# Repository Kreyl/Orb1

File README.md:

# Orb1

Project for shining orb with ws2818 leds and radio

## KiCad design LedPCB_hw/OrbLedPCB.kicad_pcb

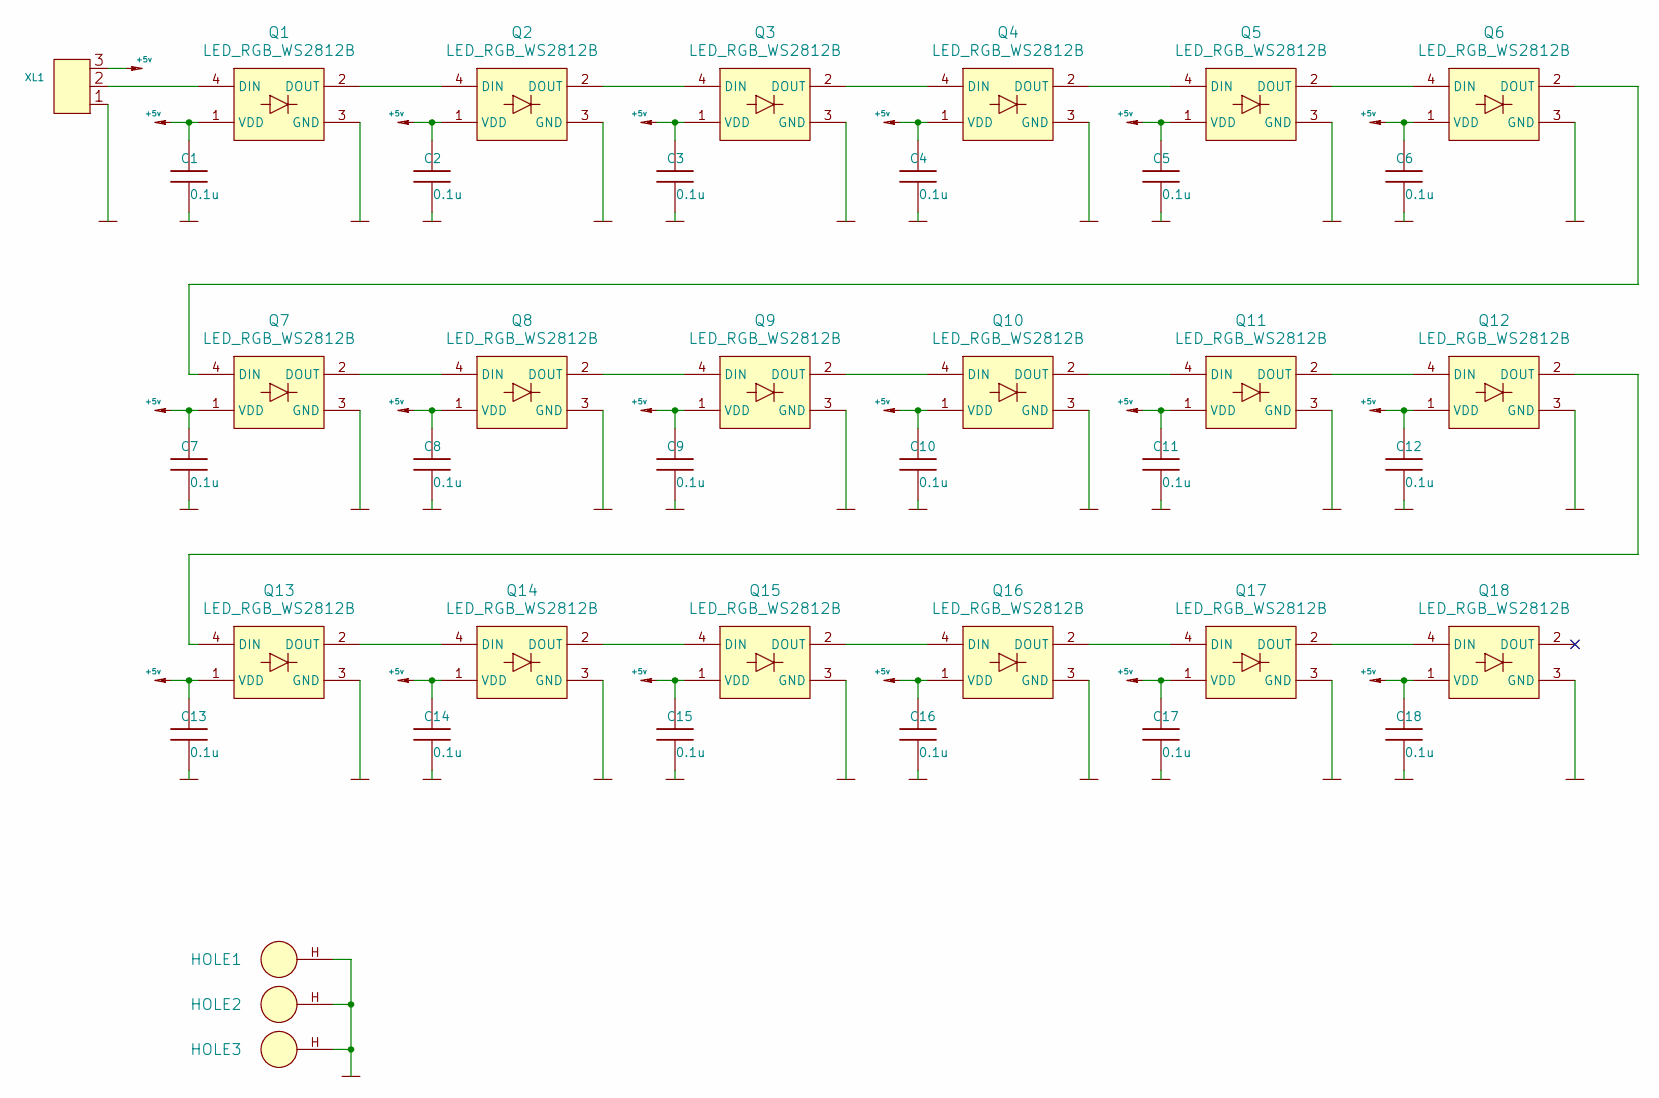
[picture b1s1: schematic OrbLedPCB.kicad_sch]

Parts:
C1, C2, C3, C4, C5, C6, C7, C8, C9, C10, C11, C12, C13, C14, C15, C16, C17, C18: 0.1u; CAP_0603_Silks; Tolerance 20%
HOLE1, HOLE2, HOLE3: HOLE_METALLED; Hole2d2_out3d5mm
Q1, Q2, Q3, Q4, Q5, Q6, Q7, Q8, Q9, Q10, Q11, Q12, Q13, Q14, Q15, Q16, Q17, Q18: LED_RGB_WS2812B; LED_WS2812B
XL1: CONN_3; WB-03(MW-3M)

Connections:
+5v: C1.1, C2.1, C3.1, C4.1, C5.1, C6.1, C7.1, C8.1, C9.1, C10.1, C11.1, C12.1, C13.1, C14.1, C15.1, C16.1, C17.1, C18.1, Q1.1 (VDD), Q2.1 (VDD), Q3.1 (VDD), Q4.1 (VDD), Q5.1 (VDD), Q6.1 (VDD), Q7.1 (VDD), Q8.1 (VDD), Q9.1 (VDD), Q10.1 (VDD), Q11.1 (VDD), Q12.1 (VDD), Q13.1 (VDD), Q14.1 (VDD), Q15.1 (VDD), Q16.1 (VDD), Q17.1 (VDD), Q18.1 (VDD), XL1.3
GND: C1.2, C2.2, C3.2, C4.2, C5.2, C6.2, C7.2, C8.2, C9.2, C10.2, C11.2, C12.2, C13.2, C14.2, C15.2, C16.2, C17.2, C18.2, HOLE1.H, HOLE2.H, HOLE3.H, Q1.3 (GND), Q2.3 (GND), Q3.3 (GND), Q4.3 (GND), Q5.3 (GND), Q6.3 (GND), Q7.3 (GND), Q8.3 (GND), Q9.3 (GND), Q10.3 (GND), Q11.3 (GND), Q12.3 (GND), Q13.3 (GND), Q14.3 (GND), Q15.3 (GND), Q16.3 (GND), Q17.3 (GND), Q18.3 (GND), XL1.1
unnamed: Q1.2 (DOUT), Q2.4 (DIN)
unnamed: Q1.4 (DIN), XL1.2 (PM)
unnamed: Q7.2 (DOUT), Q8.4 (DIN)
unnamed: Q13.2 (DOUT), Q14.4 (DIN)
unnamed: Q2.2 (DOUT), Q3.4 (DIN)
unnamed: Q8.2 (DOUT), Q9.4 (DIN)
unnamed: Q14.2 (DOUT), Q15.4 (DIN)
unnamed: Q4.2 (DOUT), Q5.4 (DIN)
unnamed: Q3.2 (DOUT), Q4.4 (DIN)
unnamed: Q10.2 (DOUT), Q11.4 (DIN)
unnamed: Q9.2 (DOUT), Q10.4 (DIN)
unnamed: Q16.2 (DOUT), Q17.4 (DIN)
unnamed: Q15.2 (DOUT), Q16.4 (DIN)
unnamed: Q5.2 (DOUT), Q6.4 (DIN)
unnamed: Q11.2 (DOUT), Q12.4 (DIN)
unnamed: Q17.2 (DOUT), Q18.4 (DIN)
unnamed: Q6.2 (DOUT), Q7.4 (DIN)
unnamed: Q12.2 (DOUT), Q13.4 (DIN)

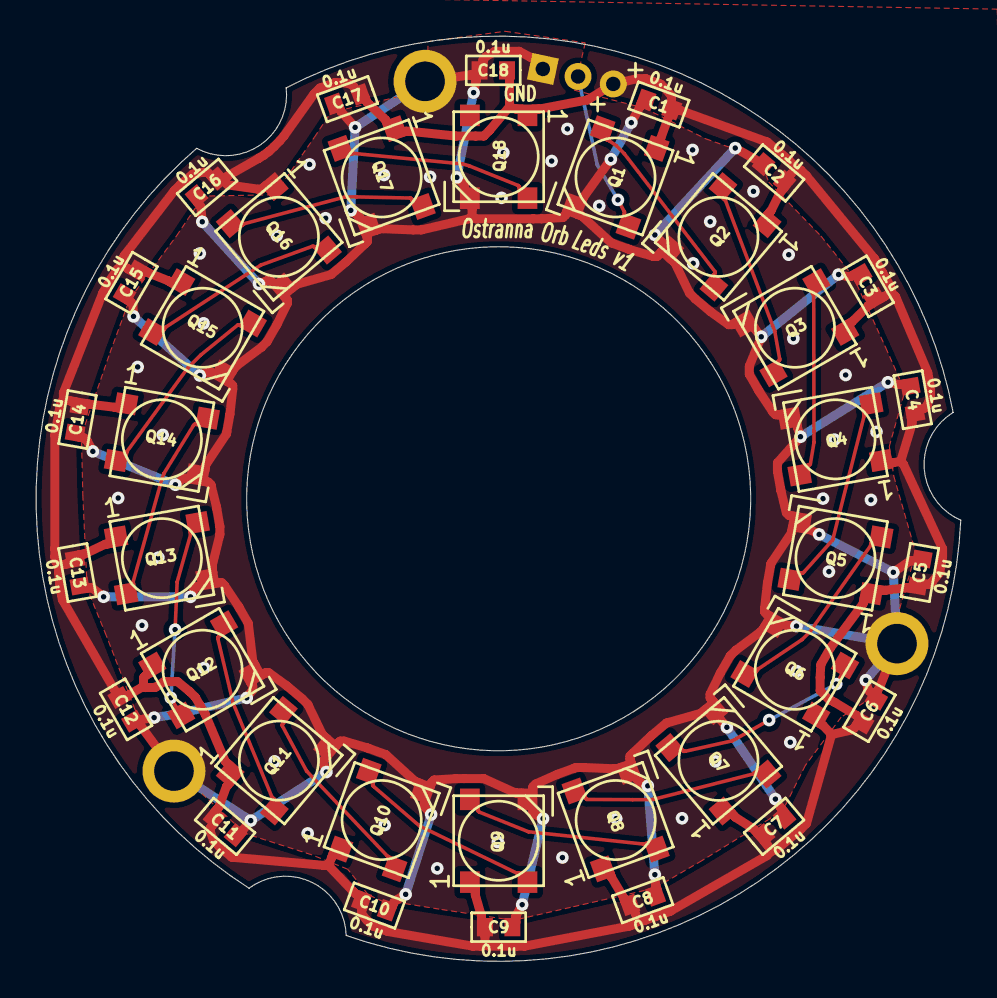
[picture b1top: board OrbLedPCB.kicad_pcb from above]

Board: 2 copper layers, 51.4 x 51.4 mm, 40 parts (1 on the bottom side), 20 nets.

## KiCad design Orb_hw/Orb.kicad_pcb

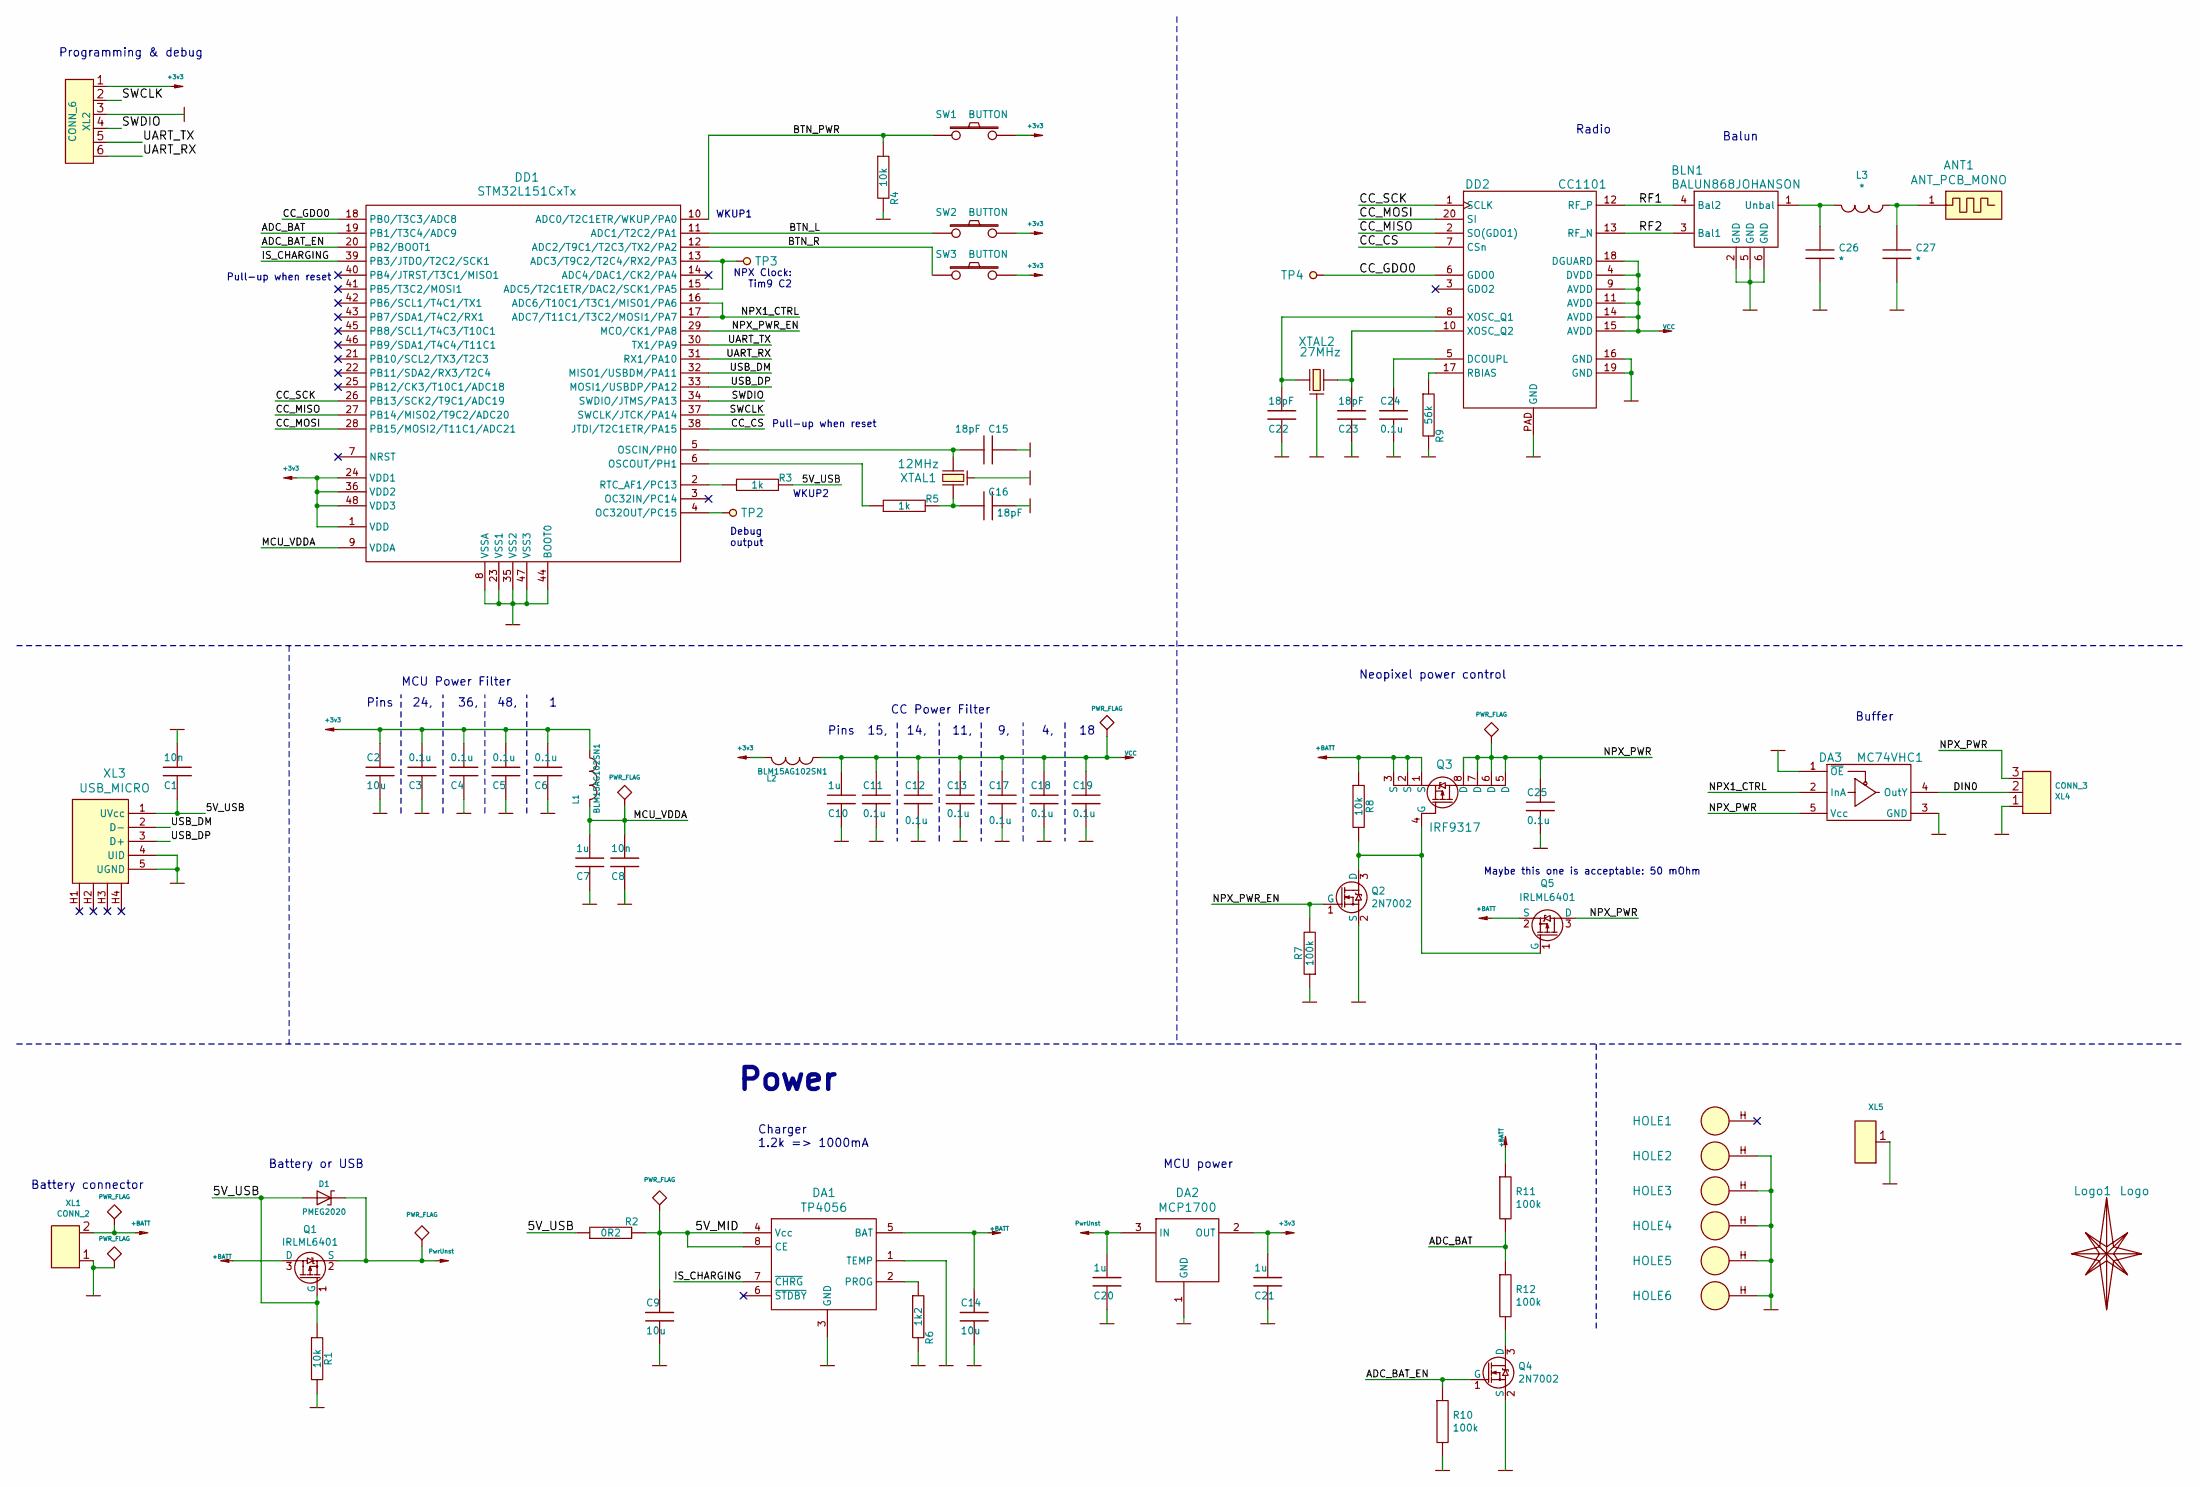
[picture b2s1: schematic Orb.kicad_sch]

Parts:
ANT1: ANT_PCB_MONO; Firefly_868
BLN1: BALUN868JOHANSON; BALUN_JOHANSON868
C1, C8: 10n; CAP_0603_Silks
C2, C9, C14: 10u; CAP_0603_Silks
C3, C4, C5, C6, C11, C12, C13, C17, C18, C19, C24, C25: 0.1u; CAP_0603_Silks
C7, C10, C20, C21: 1u; CAP_0603_Silks
C15, C16, C22, C23: 18pF; CAP_0603_Silks
C26, C27: *; CAP_0402
D1: PMEG2020; SOD323
DA1: TP4056; SO8_150MIL
DA2: MCP1700; SOT23-3A
DA3: MC74VHC1; SOT23-5
DD1: STM32L151CxTx; LQFP48
DD2: CC1101; QFN20
HOLE1, HOLE2, HOLE3, HOLE4, HOLE5, HOLE6: HOLE_METALLED; Hole2d4_out4d4mm
L1, L2: BLM15AG102SN1; IND_0402
L3: *; IND_0402
Logo1: Logo; Ostranna_16d9_13d5
Q1, Q5: IRLML6401; SOT23-3
Q2, Q4: 2N7002; SOT23-3
Q3: IRF9317; SO8_150MIL
R1, R4, R8: 10k; RES_0603
R2: 0R2; RES_1206
R3, R5: 1k; RES_0603
R6: 1k2; RES_0603
R7, R10, R11, R12: 100k; RES_0603
R9: 56k; RES_0603
SW1, SW2, SW3: BUTTON; BTN_4x4_SMD
TP2, TP3, TP4: TESTPOINT; TESTPOINT_1MM
XL1: CONN_2; SLD_2_2D5
XL2: CONN_6; PLS-6_LOCK
XL3: USB_MICRO; USBmicro_MOLEX_1050170001
XL4: CONN_3; SLD_3_2D5
XL5: CONN_1; PLS-1Square
XTAL1: 12MHz; 03225C4
XTAL2: 27MHz; 03225C4

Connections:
+3v3: C2.2, C3.1, C4.1, C5.1, C6.1, C21.1, DA2.2 (OUT), DD1.1 (VDD), DD1.24 (VDD1), DD1.36 (VDD2), DD1.48 (VDD3), L1.1, L2.2, SW1.2, SW2.2, SW3.2, XL2.1
+BATT: C14.2, DA1.5 (BAT), Q1.3 (D), Q3.1 (S), Q3.2 (S), Q3.3 (S), Q5.2 (S), R8.1, R11.1, XL1.2 (PM)
/5V_MID: C9.2, DA1.4 (Vcc), DA1.8 (CE), R2.2
/5V_USB: C1.2, D1.A, Q1.1 (G), R1.1, R2.1, R3.2, XL3.1 (UVcc)
/ADC_BAT: DD1.19 (PB1/T3C4/ADC9), R11.2, R12.1
/ADC_BAT_EN: DD1.20 (PB2/BOOT1), Q4.1 (G), R10.1
/BTN_L: DD1.11 (ADC1/T2C2/PA1), SW2.1
/BTN_PWR: DD1.10 (ADC0/T2C1ETR/WKUP/PA0), R4.1, SW1.1
/BTN_R: DD1.12 (ADC2/T9C1/T2C3/TX2/PA2), SW3.1
/CC_CS: DD1.38 (JTDI/T2C1ETR/PA15), DD2.7 (CSn)
/CC_GDO0: DD1.18 (PB0/T3C3/ADC8), DD2.6 (GDO0), TP4.1
/CC_MISO: DD1.27 (PB14/MISO2/T9C2/ADC20), DD2.2 (SO(GDO1))
/CC_MOSI: DD1.28 (PB15/MOSI2/T11C1/ADC21), DD2.20 (SI)
/CC_SCK: DD1.26 (PB13/SCK2/T9C1/ADC19), DD2.1 (SCLK)
/DIN0: DA3.4 (OutY), XL4.2 (PM)
/IS_CHARGING: DA1.7 (~CHRG), DD1.39 (PB3/JTDO/T2C2/SCK1)
/MCU_VDDA: C7.1, C8.1, DD1.9 (VDDA), L1.2
/NPX1_CTRL: DA3.2 (InA), DD1.16 (ADC6/T10C1/T3C1/MISO1/PA6), DD1.17 (ADC7/T11C1/T3C2/MOSI1/PA7)
/NPX_PWR: C25.2, DA3.5 (Vcc), Q3.5 (D), Q3.6 (D), Q3.7 (D), Q3.8 (D), Q5.3 (D), XL4.3
/NPX_PWR_EN: DD1.29 (MCO/CK1/PA8), Q2.1 (G), R7.2
/RF1: BLN1.4 (Bal2), DD2.12 (RF_P)
/RF2: BLN1.3 (Bal1), DD2.13 (RF_N)
/SWCLK: DD1.37 (SWCLK/JTCK/PA14), XL2.2
/SWDIO: DD1.34 (SWDIO/JTMS/PA13), XL2.4
/UART_RX: DD1.31 (RX1/PA10), XL2.6
/UART_TX: DD1.30 (TX1/PA9), XL2.5
/USB_DM: DD1.32 (MISO1/USBDM/PA11), XL3.2 (D-)
/USB_DP: DD1.33 (MOSI1/USBDP/PA12), XL3.3 (D+)
GND: BLN1.2 (GND), BLN1.5 (GND), BLN1.6 (GND), C1.1, C2.1, C3.2, C4.2, C5.2, C6.2, C7.2, C8.2, C9.1, C10.2, C11.2, C12.2, C13.2, C14.1, C15.2, C16.2, C17.2, C18.2, C19.2, C20.2, C21.2, C22.2, C23.2, C24.1, C25.1, C26.2, C27.2, DA1.1 (TEMP), DA1.3 (GND), DA2.1 (GND), DA3.1 (~OE), DA3.3 (GND), DD1.8 (VSSA), DD1.23 (VSS1), DD1.35 (VSS2), DD1.44 (BOOT0), DD1.47 (VSS3), DD2.16 (GND), DD2.19 (GND), DD2.PAD (GND), HOLE2.H, HOLE3.H, HOLE4.H, HOLE5.H, HOLE6.H, Q2.2 (S), Q4.2 (S), R1.2, R4.2, R6.2, R7.1, R9.2, R10.2, XL1.1, XL2.3, XL3.4 (UID), XL3.5 (UGND), XL4.1, XL5.1, XTAL1.H, XTAL2.H
unnamed: ANT1.1, C27.1, L3.2
unnamed: BLN1.1 (Unbal), C26.1, L3.1
unnamed: C15.1, DD1.5 (OSCIN/PH0), XTAL1.1
unnamed: C16.1, R5.2, XTAL1.2
unnamed: C22.1, DD2.8 (XOSC_Q1), XTAL2.1
unnamed: C23.1, DD2.10 (XOSC_Q2), XTAL2.2
unnamed: C24.2, DD2.5 (DCOUPL)
unnamed: DA1.2 (PROG), R6.1
unnamed: DD1.2 (RTC_AF1/PC13), R3.1
unnamed: DD1.4 (OC32OUT/PC15), TP2.1
unnamed: DD1.6 (OSCOUT/PH1), R5.1
unnamed: DD1.13 (ADC3/T9C2/T2C4/RX2/PA3), DD1.15 (ADC5/T2C1ETR/DAC2/SCK1/PA5), TP3.1
unnamed: DD2.17 (RBIAS), R9.1
unnamed: Q2.3 (D), Q3.4 (G), Q5.1 (G), R8.2
unnamed: Q4.3 (D), R12.2
PwrUnst: C20.1, D1.C, DA2.3 (IN), Q1.2 (S)
VCC: C10.1, C11.1, C12.1, C13.1, C17.1, C18.1, C19.1, DD2.4 (DVDD), DD2.9 (AVDD), DD2.11 (AVDD), DD2.14 (AVDD), DD2.15 (AVDD), DD2.18 (DGUARD), L2.1

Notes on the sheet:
Battery connector
Programming & debug
Pull-up when reset
Battery or USB
Pins 24, 36, 48, 1
MCU Power Filter
WKUP1
Debug output
Power
Charger 1.2k => 1000mA
NPX Clock: Tim9 C2
WKUP2
Pins 15, 14, 11, 9, 4, 18
CC Power Filter
MCU power
Neopixel power control
Radio
Maybe this one is acceptable: 50 mOhm
Balun
Buffer

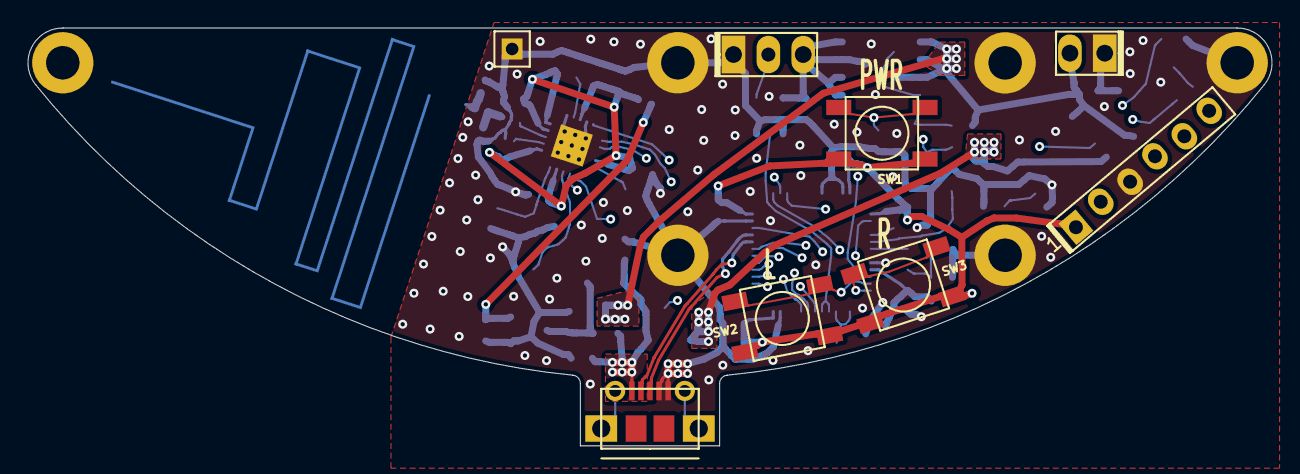
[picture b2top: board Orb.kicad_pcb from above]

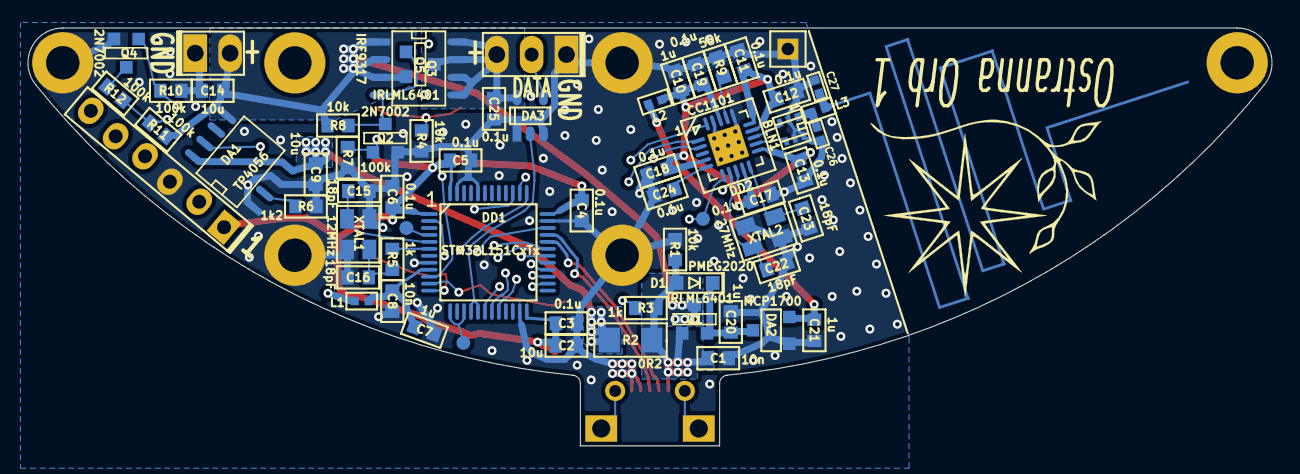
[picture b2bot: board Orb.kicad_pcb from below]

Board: 4 copper layers, 89.3 x 30.0 mm, 75 parts (61 on the bottom side), 46 nets.

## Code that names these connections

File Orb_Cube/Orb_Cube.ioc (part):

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Mcu.Name=STM32L151C(6-8-B)Tx
Mcu.Package=LQFP48
Mcu.UserName=STM32L151C8Tx
PA0-WKUP1.Mode=SYS_WakeUp0
PA0-WKUP1.Signal=SYS_WKUP1
PA1.Signal=GPIO_Input
PA10.Mode=Asynchronous
PA10.Signal=USART1_RX
PA11.Mode=Device
PA11.Signal=USB_DM
PA12.Mode=Device
PA12.Signal=USB_DP
PA13.Mode=Serial_Wire
PA13.Signal=SYS_JTMS-SWDIO
PA14.Mode=Serial_Wire
PA14.Signal=SYS_JTCK-SWCLK
PA15.Signal=GPIO_Output
PA2.Signal=GPIO_Input
PA3.Signal=S_TIM9_CH2
PA5.Mode=TX_Only_Simplex_Unidirect_Slave
PA5.Signal=SPI1_SCK
PA6.Mode=TX_Only_Simplex_Unidirect_Slave
PA6.Signal=SPI1_MISO
PA8.Signal=GPIO_Output
PA9.Mode=Asynchronous
PA9.Signal=USART1_TX
PB0.Signal=GPIO_Input
PB1.Mode=IN9
PB1.Signal=ADC_IN9
PB13.Mode=Full_Duplex_Master
PB13.Signal=SPI2_SCK
PB14.Mode=Full_Duplex_Master
PB14.Signal=SPI2_MISO
PB15.Mode=Full_Duplex_Master
PB15.Signal=SPI2_MOSI
PB2.Signal=GPIO_Output
PB3.Signal=GPIO_Input
PC13-WKUP2.Mode=SYS_WakeUp1
PC13-WKUP2.Signal=SYS_WKUP2
PH0-OSC_IN.Mode=HSE-External-Oscillator
PH0-OSC_IN.Signal=RCC_OSC_IN
PH1-OSC_OUT.Mode=HSE-External-Oscillator
PH1-OSC_OUT.Signal=RCC_OSC_OUT
RCC.HSE_VALUE=12000000
RCC.SYSCLKFreq_VALUE=24000000
RCC.SYSCLKSource=RCC_SYSCLKSOURCE_PLLCLK
board=custom

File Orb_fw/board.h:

#pragma once

// ==== General ====
#define BOARD_NAME          "Orb1"
#define APP_NAME            "Orb1"

#ifndef TRUE
#define TRUE    1
#endif

// ==== High-level peripery control ====
#define PILL_ENABLED        FALSE
#define BEEPER_ENABLED      FALSE
#define BUTTONS_ENABLED     TRUE

#define SIMPLESENSORS_ENABLED   TRUE

// MCU type as defined in the ST header.
#define STM32L151xB

// Freq of external crystal if any. Leave it here even if not used.
#define CRYSTAL_FREQ_HZ 12000000

// OS timer settings
#define STM32_ST_IRQ_PRIORITY   2
#define STM32_ST_USE_TIMER      2
#define STM32_TIMCLK1           (Clk.APB1FreqHz)

#define ADC_REQUIRED    TRUE

// LEDs config: BandCnt; {LedCnt1, LedCnt2, LedCnt3...}
#define BAND_CNT        1
#define BAND_SETUPS     ((const BandSetup_t[]){\
    {18, dirForward}, \
    })

#if 1 // ========================== GPIO =======================================
// PortMinTim_t: GPIO, Pin, Tim, TimChnl, invInverted, omPushPull, TopValue
// UART
#define UART_GPIO       GPIOA
#define UART_TX_PIN     9
#define UART_RX_PIN     10

// Buttons
#define BTN1_PIN        GPIOA, 0
#define BTN2_PIN        GPIOA, 1, pudPullDown
#define BTN3_PIN        GPIOA, 2, pudPullDown

// Charging & USB
#define IS_CHARGING_PIN GPIOB, 3
#define PIN_5V_USB      GPIOC, 13

// Npx LEDs
#define NPX_SPI         SPI1
#define NPX_DATA_PIN    GPIOA, 7, AF5
#define NPX_PWR_PIN     GPIOA, 8
//#define NPX_GENER_PIN   GPIOA, 3, TIM9, 2, invNotInverted, omPushPull, 255

// ADC
#define ADC_BAT_EN      GPIOB, 2
#define ADC_BAT_PIN     GPIOB, 1

#endif // GPIO

#if ADC_REQUIRED // ======================= Inner ADC ==========================
#define BAT_CHNL            9
#define ADC_VREFINT_CHNL    17  // All 4xx, F072 and L151 devices. Do not change.
#define ADC_CHANNELS        { BAT_CHNL, ADC_VREFINT_CHNL }
#define ADC_CHANNEL_CNT     2   // Do not use countof(AdcChannels) as preprocessor does not know what is countof => cannot check
#define ADC_SAMPLE_TIME     ast96Cycles
#define ADC_SAMPLE_CNT      8   // How many times to measure every channel
#define ADC_SEQ_LEN         (ADC_SAMPLE_CNT * ADC_CHANNEL_CNT)
#endif

#if 1 // =========================== DMA =======================================
#define STM32_DMA_REQUIRED  TRUE
// ==== Uart ====
#define UART_DMA_TX_MODE(Chnl) (STM32_DMA_CR_CHSEL(Chnl) | DMA_PRIORITY_LOW | STM32_DMA_CR_MSIZE_BYTE | STM32_DMA_CR_PSIZE_BYTE | STM32_DMA_CR_MINC | STM32_DMA_CR_DIR_M2P | STM32_DMA_CR_TCIE)
#define UART_DMA_RX_MODE(Chnl) (STM32_DMA_CR_CHSEL(Chnl) | DMA_PRIORITY_MEDIUM | STM32_DMA_CR_MSIZE_BYTE | STM32_DMA_CR_PSIZE_BYTE | STM32_DMA_CR_MINC | STM32_DMA_CR_DIR_P2M | STM32_DMA_CR_CIRC)
#define UART_DMA_TX     STM32_DMA_STREAM_ID(1, 4)
#define UART_DMA_RX     STM32_DMA_STREAM_ID(1, 5)
#define UART_DMA_CHNL   0   // Dummy

// ==== Npx ====
#define NPX_DMA         STM32_DMA_STREAM_ID(1, 3)  // SPI1 TX

#if ADC_REQUIRED
#define ADC_DMA         STM32_DMA_STREAM_ID(1, 1)
#define ADC_DMA_MODE    STM32_DMA_CR_CHSEL(0) |   /* dummy */ \
                        DMA_PRIORITY_LOW | \
                        STM32_DMA_CR_MSIZE_HWORD | \
                        STM32_DMA_CR_PSIZE_HWORD | \
                        STM32_DMA_CR_MINC |       /* Memory pointer increase */ \
                        STM32_DMA_CR_DIR_P2M |    /* Direction is peripheral to memory */ \
                        STM32_DMA_CR_TCIE         /* Enable Transmission Complete IRQ */
#endif // ADC

#endif // DMA

#if 1 // ========================== USART ======================================
#define PRINTF_FLOAT_EN FALSE
#define UART_TXBUF_SZ   512
#define UART_RXBUF_SZ   1024
#define CMD_BUF_SZ      128

#define CMD_UART        USART1

#define UARTS_CNT       1

#define CMD_UART_PARAMS \
    CMD_UART, UART_GPIO, UART_TX_PIN, UART_GPIO, UART_RX_PIN, \
    UART_DMA_TX, UART_DMA_RX, UART_DMA_TX_MODE(UART_DMA_CHNL), UART_DMA_RX_MODE(UART_DMA_CHNL)

#endif

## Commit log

2020-05-31 First
2020-05-31 - .sch
2020-06-01 + Sent to factory
2020-06-04 + LedPCB
2020-06-05 Started work on mic orb
2020-06-10 + FW started
2020-06-14 + OrbRing Not smmothly
2020-06-14 + Smooth average
2020-06-16 Flare clean-up
2020-06-18 Starts and ends at same point
2020-06-18 + Smooth flares + Random params
2020-06-19 Two flares in sync: next starts when first is starting to fade.
2020-06-19 + Timer-based fade
2020-06-19 + Set hsv
2020-06-20 + On-off layer
2020-06-22 + Alque Release
2020-06-24 + Pwron on long press + Pwron src
2020-06-25 + Off when discharged * States mech improved to avoid race conditions
2020-06-25 + Bounds change
2020-06-25 + Save/load color bounds
2020-06-27 * Diag
2020-10-02 + WS2812 v2
2021-07-20 Smth
2021-09-04 + Three Timers RC
